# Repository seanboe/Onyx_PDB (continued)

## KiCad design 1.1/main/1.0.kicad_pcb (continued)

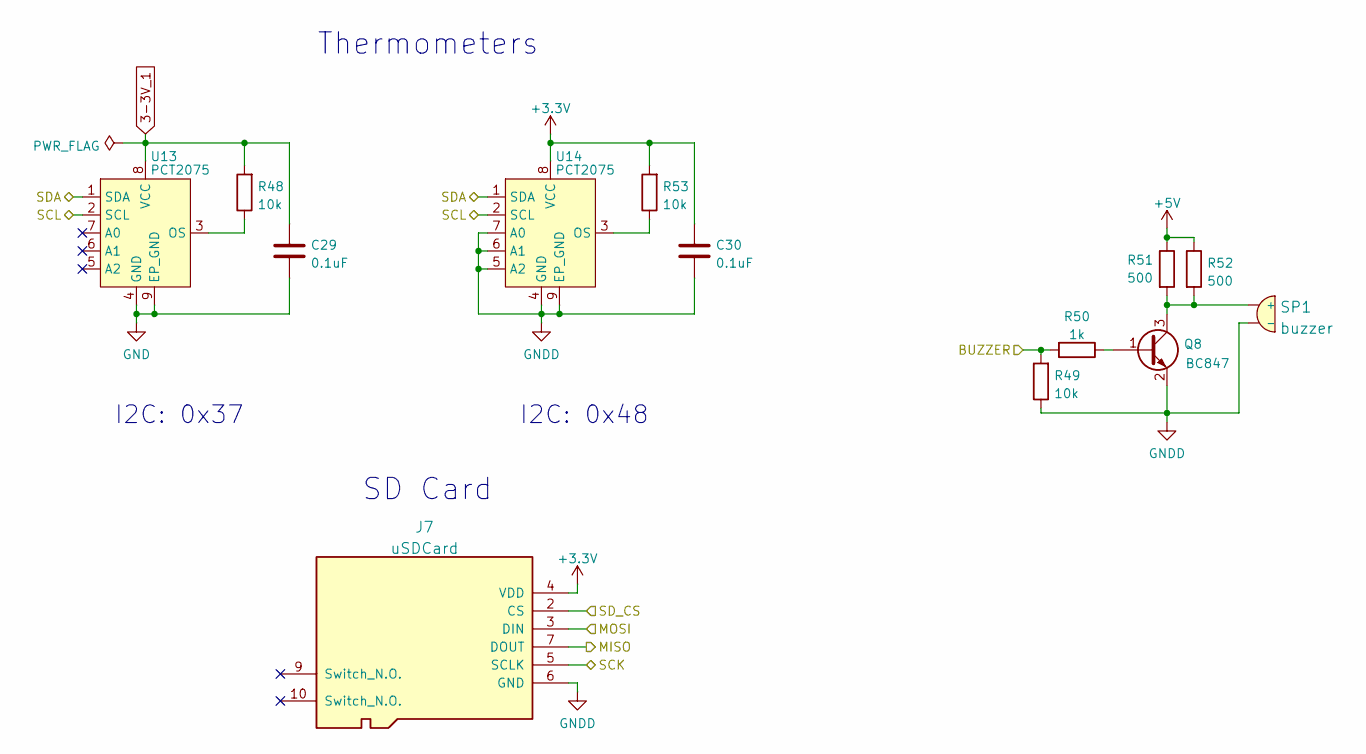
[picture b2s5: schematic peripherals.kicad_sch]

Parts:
C29, C30: 0.1uF; C_1608_603_B
J7: uSDCard; uSDCard_SD_503182_011
Q8: BC847; SOT-23
R48, R49, R53: 10k; R_1608_603_B
R50: 1k; R_1608_603_B
R51, R52: 500; R_2012_805_B
SP1: buzzer; 13-9mm_Buzzer
U13, U14: PCT2075; PCT2075TP_147

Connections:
3-3V_1: C29.2, R48.2, U13.8 (VCC); also elsewhere on the board
+3V3: C30.2, J7.4 (VDD), R53.2, U14.8 (VCC); also elsewhere on the board
+5V: R51.1, R52.1; also elsewhere on the board
/BUZZER: R49.2, R50.2; also elsewhere on the board
/MISO: J7.7 (DOUT); also elsewhere on the board
/MOSI: J7.3 (DIN); also elsewhere on the board
/SCK: J7.5 (SCLK); also elsewhere on the board
/SCL: U13.2 (SCL), U14.2 (SCL); also elsewhere on the board
/SDA: U13.1 (SDA), U14.1 (SDA); also elsewhere on the board
/SD_CS: J7.2 (CS); also elsewhere on the board
GND: C29.1, U13.4 (GND), U13.9 (EP_GND); also elsewhere on the board
GNDD: C30.1, J7.6 (GND), Q8.2 (E), R49.1, SP1.2 (-), U14.4 (GND), U14.5 (A2), U14.6 (A1), U14.7 (A0), U14.9 (EP_GND); also elsewhere on the board
unnamed: Q8.1 (B), R50.1
unnamed: Q8.3 (C), R51.2, R52.2, SP1.1 (+)
unnamed: R48.1, U13.3 (OS)
unnamed: R53.1, U14.3 (OS)

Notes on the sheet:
I2C: 0x48
SD Card
I2C: 0x37
Thermometers

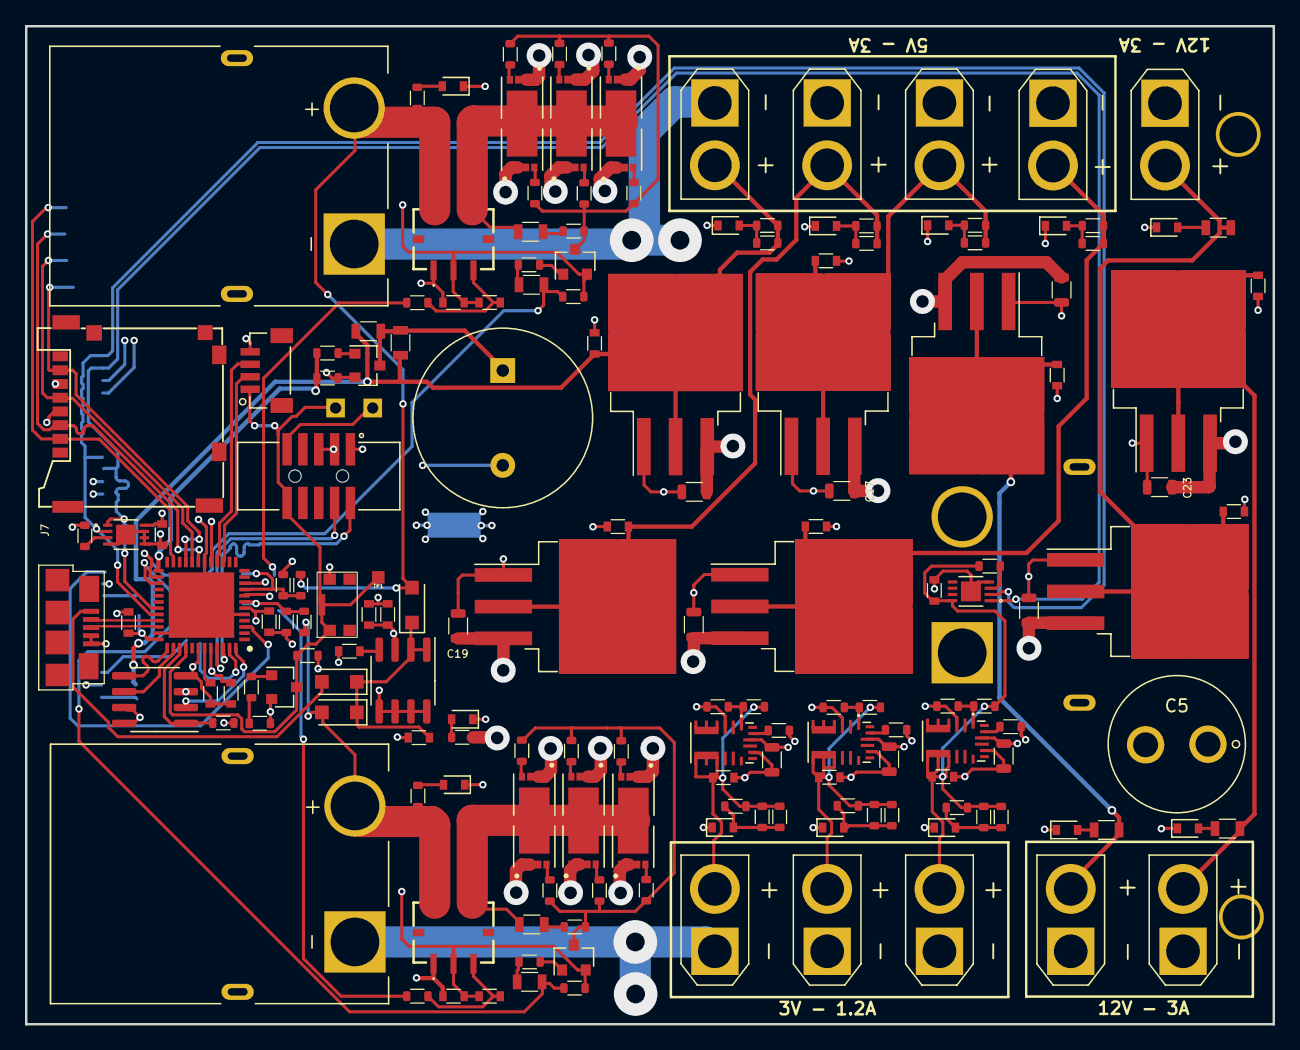
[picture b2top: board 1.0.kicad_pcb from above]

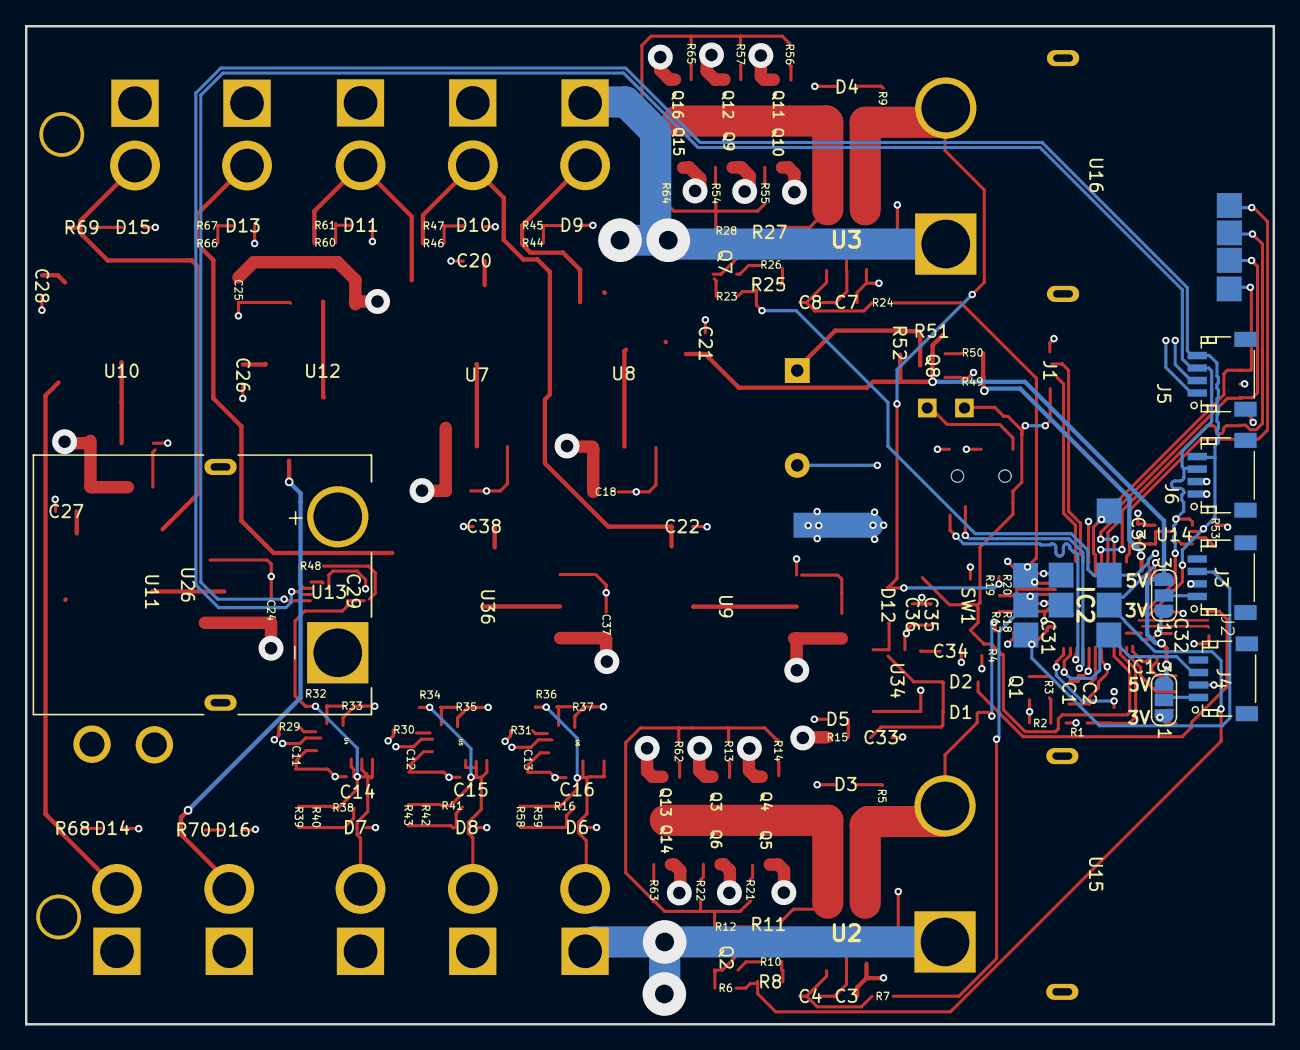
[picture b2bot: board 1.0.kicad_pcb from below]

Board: 4 copper layers, 100.0 x 80.0 mm, 199 parts (22 on the bottom side), 98 nets.

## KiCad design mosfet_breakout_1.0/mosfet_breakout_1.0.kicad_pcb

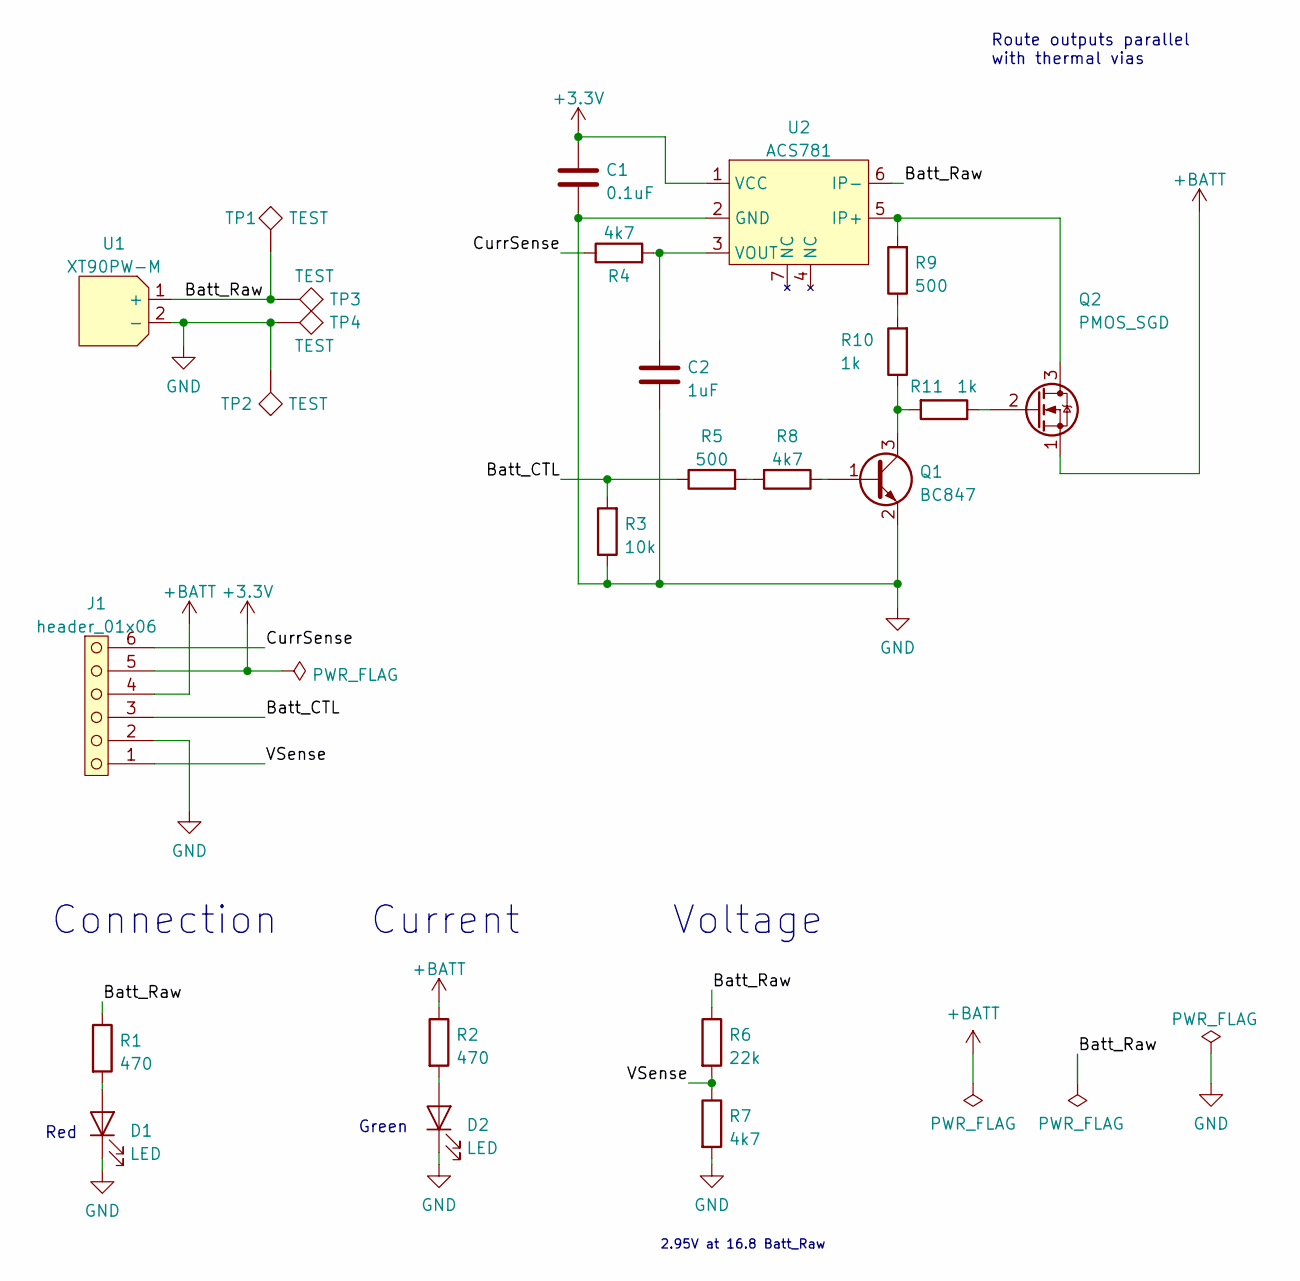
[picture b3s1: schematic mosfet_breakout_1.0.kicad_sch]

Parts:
C1: 0.1uF; C_1608_603_B
C2: 1uF; C_1608_603_B
D1, D2: LED; R_1608_603_B
J1: header_01x06; header_01x06_pitch2.54_tht
Q1: BC847; SOT-23
Q2: PMOS_SGD; VDFN-8
R1, R2: 470; R_1608_603_B
R3: 10k; R_1608_603_B
R4, R7, R8: 4k7; R_1608_603_B
R5, R9: 500; R_2012_805_B
R6: 22k; R_1608_603_B
R10, R11: 1k; R_1608_603_B
TP1, TP2, TP3, TP4: TEST; test_point_5mm_square
U1: XT90PW-M; AMASS_XT90PW-M_Horizontal
U2: ACS781; 7-LR-PSOF

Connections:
+3V3: C1.2, J1.5, U2.1 (VCC)
+BATT: J1.4, Q2.1 (S), R2.1
/Batt_CTL: J1.3, R3.2, R5.1
/Batt_Raw: R1.1, R6.1, TP1.1, TP3.1, U1.1 (+), U2.6 (IP-)
/CurrSense: J1.6, R4.1
/VSense: J1.1, R6.2, R7.1
GND: C1.1, C2.1, D1.1 (K), D2.1 (K), J1.2, Q1.2 (E), R3.1, R7.2, TP2.1, TP4.1, U1.2 (-), U2.2 (GND)
unnamed: C2.2, R4.2, U2.3 (VOUT)
unnamed: D1.2 (A), R1.2
unnamed: D2.2 (A), R2.2
unnamed: Q1.1 (B), R8.1
unnamed: Q1.3 (C), R10.1, R11.2
unnamed: Q2.2 (G), R11.1
unnamed: Q2.3 (D), R9.2, U2.5 (IP+)
unnamed: R5.2, R8.2
unnamed: R9.1, R10.2

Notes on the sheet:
2.95V at 16.8 Batt_Raw
Red
Current
Route outputs parallel with thermal vias
Connection
Green
Voltage

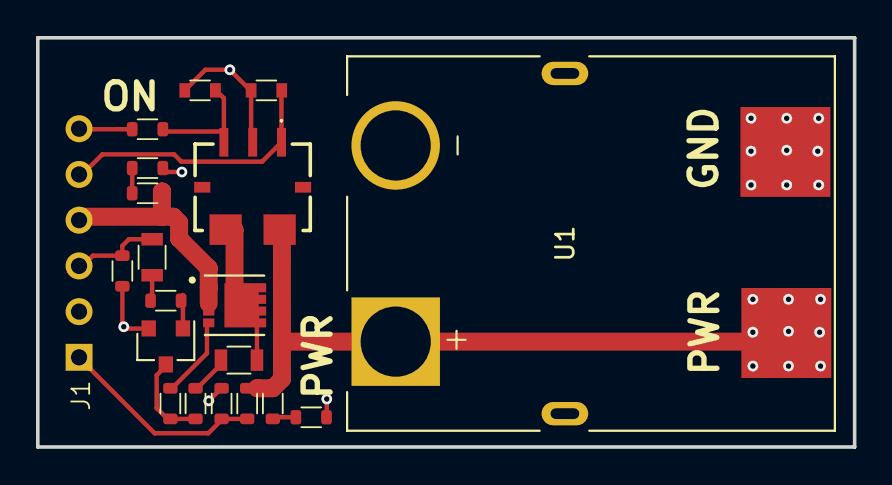
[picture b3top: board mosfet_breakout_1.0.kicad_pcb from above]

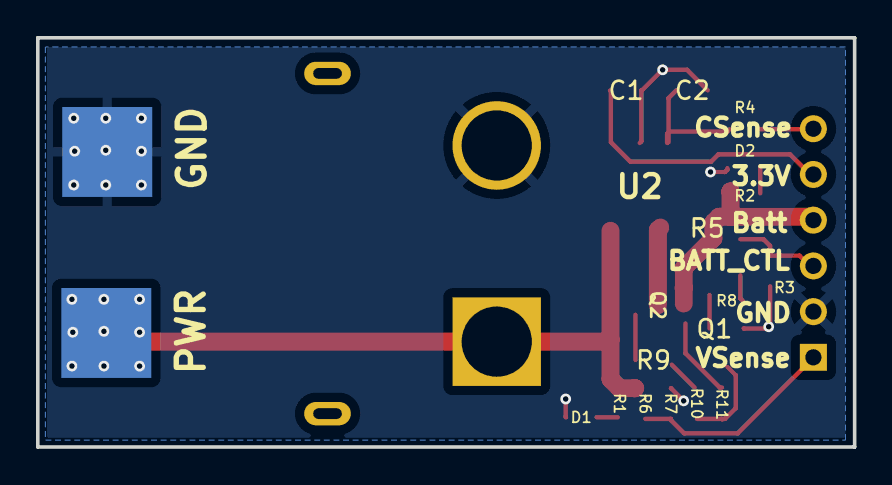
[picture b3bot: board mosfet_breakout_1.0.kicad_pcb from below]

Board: 2 copper layers, 45.4 x 22.7 mm, 24 parts (2 on the bottom side), 16 nets.
